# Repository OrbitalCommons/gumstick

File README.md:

# Gumstick: ESP32 + iCE40 FPGA module

A small "gumstick" daughterboard that pairs an Espressif ESP32 (Wi-Fi, USB,
application CPU) with a Lattice iCE40UP5K FPGA (timing-critical I/O), plus the
carrier used to program and test it. KiCad 10 sources, fabrication outputs,
interface control documents and the scripts that generated them.

| Folder | Design | Status |
|---|---|---|
| [`current-df40-connectors/`](current-df40-connectors/README.md) | **v1, current.** 20 × 45 mm, 4 layers, ESP32-S2FH4 + iCE40UP5K-SG48, U.FL antenna jack, RGB LED, two underside Hirose DF40 40-pin board-to-board connectors (one receptacle, one plug, so it cannot mate reversed). | First 10 ordered; the exact ordered files are frozen in [`releases/v1/`](current-df40-connectors/releases/v1/README.md) and Git tag `v1`. |
| [`future-m2-goldfingers/`](future-m2-goldfingers/README.md) | **v2, future.** 22 × 42 mm M.2 2242 key-M card (0.8 mm, 4 layers) with gold-finger contacts and a custom pinout; bare ESP32-C6 + 16 MB QSPI flash + the same iCE40UP5K. Not PCIe/NVMe compatible. | Development draft, not for fabrication. |
| [`programming-carrier/`](programming-carrier/README.md) | USB programmer and slow-GPIO indicator fixture for the v1 module (mating DF40 pair, buttons, LEDs). | v1 ordered. |

Start with the **[v1 interface control document](current-df40-connectors/docs/ICD-v1.md)**
when designing a carrier for the module: it is the electrical and mechanical
contract (pinout, mated height, keep-outs, reusable footprints).

## Renders and 3D views

Rendered with KiCad 10 (`kicad-cli pcb render`) from the board files in this
repository. Click an STL link to open GitHub's interactive 3D viewer (board,
pads and component bodies; untextured).

### v1: ESP32-S2 + iCE40, DF40 connectors (current)

3D: [current-df40-connectors.stl](https://github.com/OrbitalCommons/gumstick/blob/main/current-df40-connectors/renders/current-df40-connectors.stl)

### v2: ESP32-C6 + iCE40, M.2 gold fingers (future)

3D: [future-m2-goldfingers.stl](https://github.com/OrbitalCommons/gumstick/blob/main/future-m2-goldfingers/renders/future-m2-goldfingers.stl)

### Programming carrier

3D: [programming-carrier.stl](https://github.com/OrbitalCommons/gumstick/blob/main/programming-carrier/renders/programming-carrier.stl)

Colour 3D models with tracks, soldermask and silkscreen are next to each STL
as `renders/<folder>.glb` (open in any glTF viewer, e.g. Blender or a browser
glTF viewer); v1 also has a STEP model in `current-df40-connectors/fab/`.

## Known carriers

- [StratumZero](https://github.com/OrbitalCommons/stratumzero)
  (OrbitalCommons, currently private): a GNSS-disciplined reference clock you
  can point a camera at, built around the v1 module.

## Working on the designs (kicadmium)

These boards are set up for the
[kicadmium](https://github.com/meawoppl/agent-portal-plugins/tree/main/kicadmium)
Agent Portal plugin. [`.kicad-pcb.json`](.kicad-pcb.json) declares the three
projects (`esp32-fpga-module`, `esp32-fpga-module-v2`, `programming-carrier`)
and the quality profile in [`docs/pcb-playbook/`](docs/pcb-playbook/README.md);
[`AGENTS.md`](AGENTS.md) has the one-time setup. Then:

```sh
agent-portal plugin open kicadmium        # open the workbench, add ?project=esp32-fpga-module
kicadmium drc --json --cwd . --project esp32-fpga-module
kicadmium kct -- lint run current-df40-connectors/module.kicad_pcb --format json > /tmp/lint.json
```

Each board folder is self-contained: its symbol and footprint libraries
(`Module.pretty`, `Module.kicad_sym`, ...) and 3D models live beside the board
and are referenced through `${KIPRJMOD}`. Datasheets cited by the designs are
in [`libraries/datasheets/`](libraries/datasheets/README.md).

## Scripts

`tools/hardware/` holds the Python (KiCad `pcbnew`) and C++ helpers used to
place, route, audit and export the boards. They are kept for reproducibility
and are not required to open or fabricate the designs. A few of the earliest
v1 scripts (`extract_module.py`, `build_placement.py`, `add_rgb.py`) read the
original MainBoard import the module was extracted from; that reference board
remains in [meawoppl/bp-test](https://github.com/meawoppl/bp-test/tree/master/boards/mainboard-reference).

## History

This repository was split out of [meawoppl/bp-test](https://github.com/meawoppl/bp-test)
with history preserved for these paths. Folder moves:
`boards/esp32-fpga-module` → `current-df40-connectors`,
`boards/esp32-fpga-module-v2` → `future-m2-goldfingers`,
`boards/programming-carrier` → `programming-carrier`.

## License

[MIT](LICENSE). Third-party datasheets and vendor 3D models included for
reference keep their own terms; see `NOTICE`.

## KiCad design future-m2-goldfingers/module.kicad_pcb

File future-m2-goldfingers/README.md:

# ESP32-C6 + iCE40UP5K M.2 module (v2, development draft)

Successor to `current-df40-connectors`: the same iCE40UP5K-SG48 FPGA and QSPI configuration link,
with the ESP32-S2 module replaced by a bare ESP32-C6 (QFN40) plus a 16 MB quad SPI flash, and the board-to-board connector replaced
by an M.2 2242 key-M card edge with a custom pinout. **Not PCIe/NVMe compatible. Not for fabrication yet.**

| Item | Value |
| --- | --- |
| Card | 22 x 42 mm, 0.8 mm (M.2 0.8 +/- 0.08), 4 layers, JLCPCB JLC04081H-3313 (nominal 0.799 mm) |
| Layers | F.Cu parts and signals, In1 GND, In2 +3.3 V (with a +1.2 V island under U2), B.Cu ESP bus and FPGA lanes |
| Contacts | 67 (positions 59-66 are the key notch); pinout in `docs/icd-v2-pinout.csv` |
| Power in | +3.3 V on 2/4/70/72/74, GND on 1/3/9/15/21/27/39/45/51/57/71/73/75 (33 now carries ESP_GPIO4) |
| MCU | ESP32-C6 QFN40 (U1), external 16 MB W25Q128JV flash (U4, QIO); 13 GPIOs + USB + EN on the connector |
| Core | TLV75512 1.2 V LDO (U3), PLL fed through L2 |
| RF | ESP32-C6 pin 1 -> C1/L3/C2 pi match -> U.FL J3, 50 ohm coated CPWG 0.14 mm / 0.15 mm gap on 0.0994 mm 3313 prepreg (`docs/rf-feed.json`); match values still to re-tune |

## Files

- `module.kicad_pro/.kicad_sch/.kicad_pcb`, `module.kicad_dru`, `Module2.pretty/`, `Module2.kicad_sym`, `3dmodels/`.
- `docs/design-contract.json`: what was agreed before layout plus the final pin/contact tables.
- `docs/icd-v2-pinout.csv`: every contact with its side (odd = front copper, even = back copper), signal, IC pad and constraint.
- `docs/c6-fpga-link.csv`: the ESP32-C6 GPIO / QFN40 pad / SG48 pad mapping of the configuration link.
- `docs/contact-assignment.json`, `docs/circuit.json`, `docs/placement.json`: generator outputs.
- `docs/validation.json`, `docs/module-schematic.pdf`, `docs/module-*.svg`: checks and review exports.

## Regenerating

```sh
/usr/bin/python3 tools/hardware/build_module_v2.py --replace-draft   # libraries, placement, outline, zones, project settings
/usr/bin/python3 tools/hardware/module_v2_route.py                   # all copper, +1.2 V island, lint via roles
/usr/bin/python3 tools/hardware/module_v2_schematic.py               # symbols and schematic from docs/circuit.json
/usr/bin/python3 tools/hardware/module_v2_docs.py                    # ICD CSVs and contract tables from the board
/usr/bin/python3 tools/hardware/check_module_v2.py                   # ERC, parity DRC, PDF/SVG exports
```

## Known compromises (see `layout.deviations` in the contract)

- Eight ground vias sit in the two exposed pads. The playbook forbids vias under packages; a grounded exposed pad has no other return path, so these are kept deliberately.
- C48, C50 (FPGA VCCIO_2 / VCC east) and C39 (VDDA1) return to ground through the front pour rather than a dedicated via.
- The 3.3 V input bulk sits at the power contacts: C67/C60 feed straight into the contact 70/72 vias, C61/C66 into the contact 2 via.
- Decoupling further than 2 mm: U2 pin 5 (2.9 mm), U2 pin 29 (2.9 mm), U2 pin 33 (3.7 mm, plane via at the pin), U1 VDDA3P3 (3.6 mm to the pi filter), U1 VDDPST1 (2.7 mm) and VDDPST2 (2.4 mm), both boxed in by the 0.4 mm-pitch fan-out. Each of these pins has an I/O exit on both neighbours at 0.5 mm pitch, so only a cap lying on the pin's own line fits and adjacent lines cannot both carry one; the contract records the per-pin reason.
- The QSPI link runs through the GPIO matrix on every lane (no native FSPI pins are free of strapping/USB duties); verify the achievable configuration clock.
- The flash (U4, W25Q128JVPIQ) runs from the 3.3 V plane and the ESP's VDD_SPI pin is left unconnected: that pin sits between the flash data pins, so its 0.1/1 uF pair has no room. U4 has 0.1 uF at its supply pin and C33 (10 uF) 4 mm away.
- The flash pin order is mirrored against the ESP's SPI pins, so WP and DO cross under CS on the back layer above U4 (four vias).
- L5 (24 nH, 0201) still needs an LCSC part number.

## Card edge (JLCPCB gold-finger rules, see `layout.card_edge` in the contract)

- ENIG finish with the gold-finger option; 30 degree bevel (JLCPCB offers 30/45, the M.2 drawing shows 20: confirm socket fit).
- Fingers stop 0.6 mm inside the routed edge (JLCPCB's copper setback for a 30 degree bevel, scaled from 1.13 mm at 1.6 mm); their inner ends stay at 2.0 / 2.5 mm.
- The finger field has one solder-mask window per side and a rule area that keeps pours and vias out of it.
- JLCPCB needs at least 50 x 50 mm for a board with gold fingers (and >= 5 x 5 cm for a chamfer), so the 22 x 42 mm card must be ordered as a panel with the connector edge on the panel outline and no V-cut through the fingers.

## Stackup

- M.2 fixes the card at 0.8 +/- 0.08 mm. JLCPCB's 0.8 mm four-layer builds range from 0.721 to 0.803 mm nominal, and their tolerance below 1.0 mm is +/- 0.1 mm. JLC04081H-3313 (0.799 mm) is the best-centred build; order it by name with impedance control and confirm the finished thickness over the fingers.
- Layers: 35 um Cu / 0.0994 mm 3313 prepreg (er 4.1) / In1 GND / 0.5 mm core / In2 +3.3 V / 0.0994 mm 3313 / 35 um Cu.
- The RF width comes from `tools/hardware/module_v2_impedance.py`: JLCPCB's coated-CPWG calculator gives 50.4 ohm and a 2D field solve 49.9 ohm for 0.14 mm / 0.15 mm.

## Open before any fabrication

Carrier design and socket fit (TE 1-2199230-6), 0.8 mm stackup selection and RF/USB re-calculation, antenna match,
finger plating/bevel confirmation against the socket drawing, firmware bring-up of the C6 target.

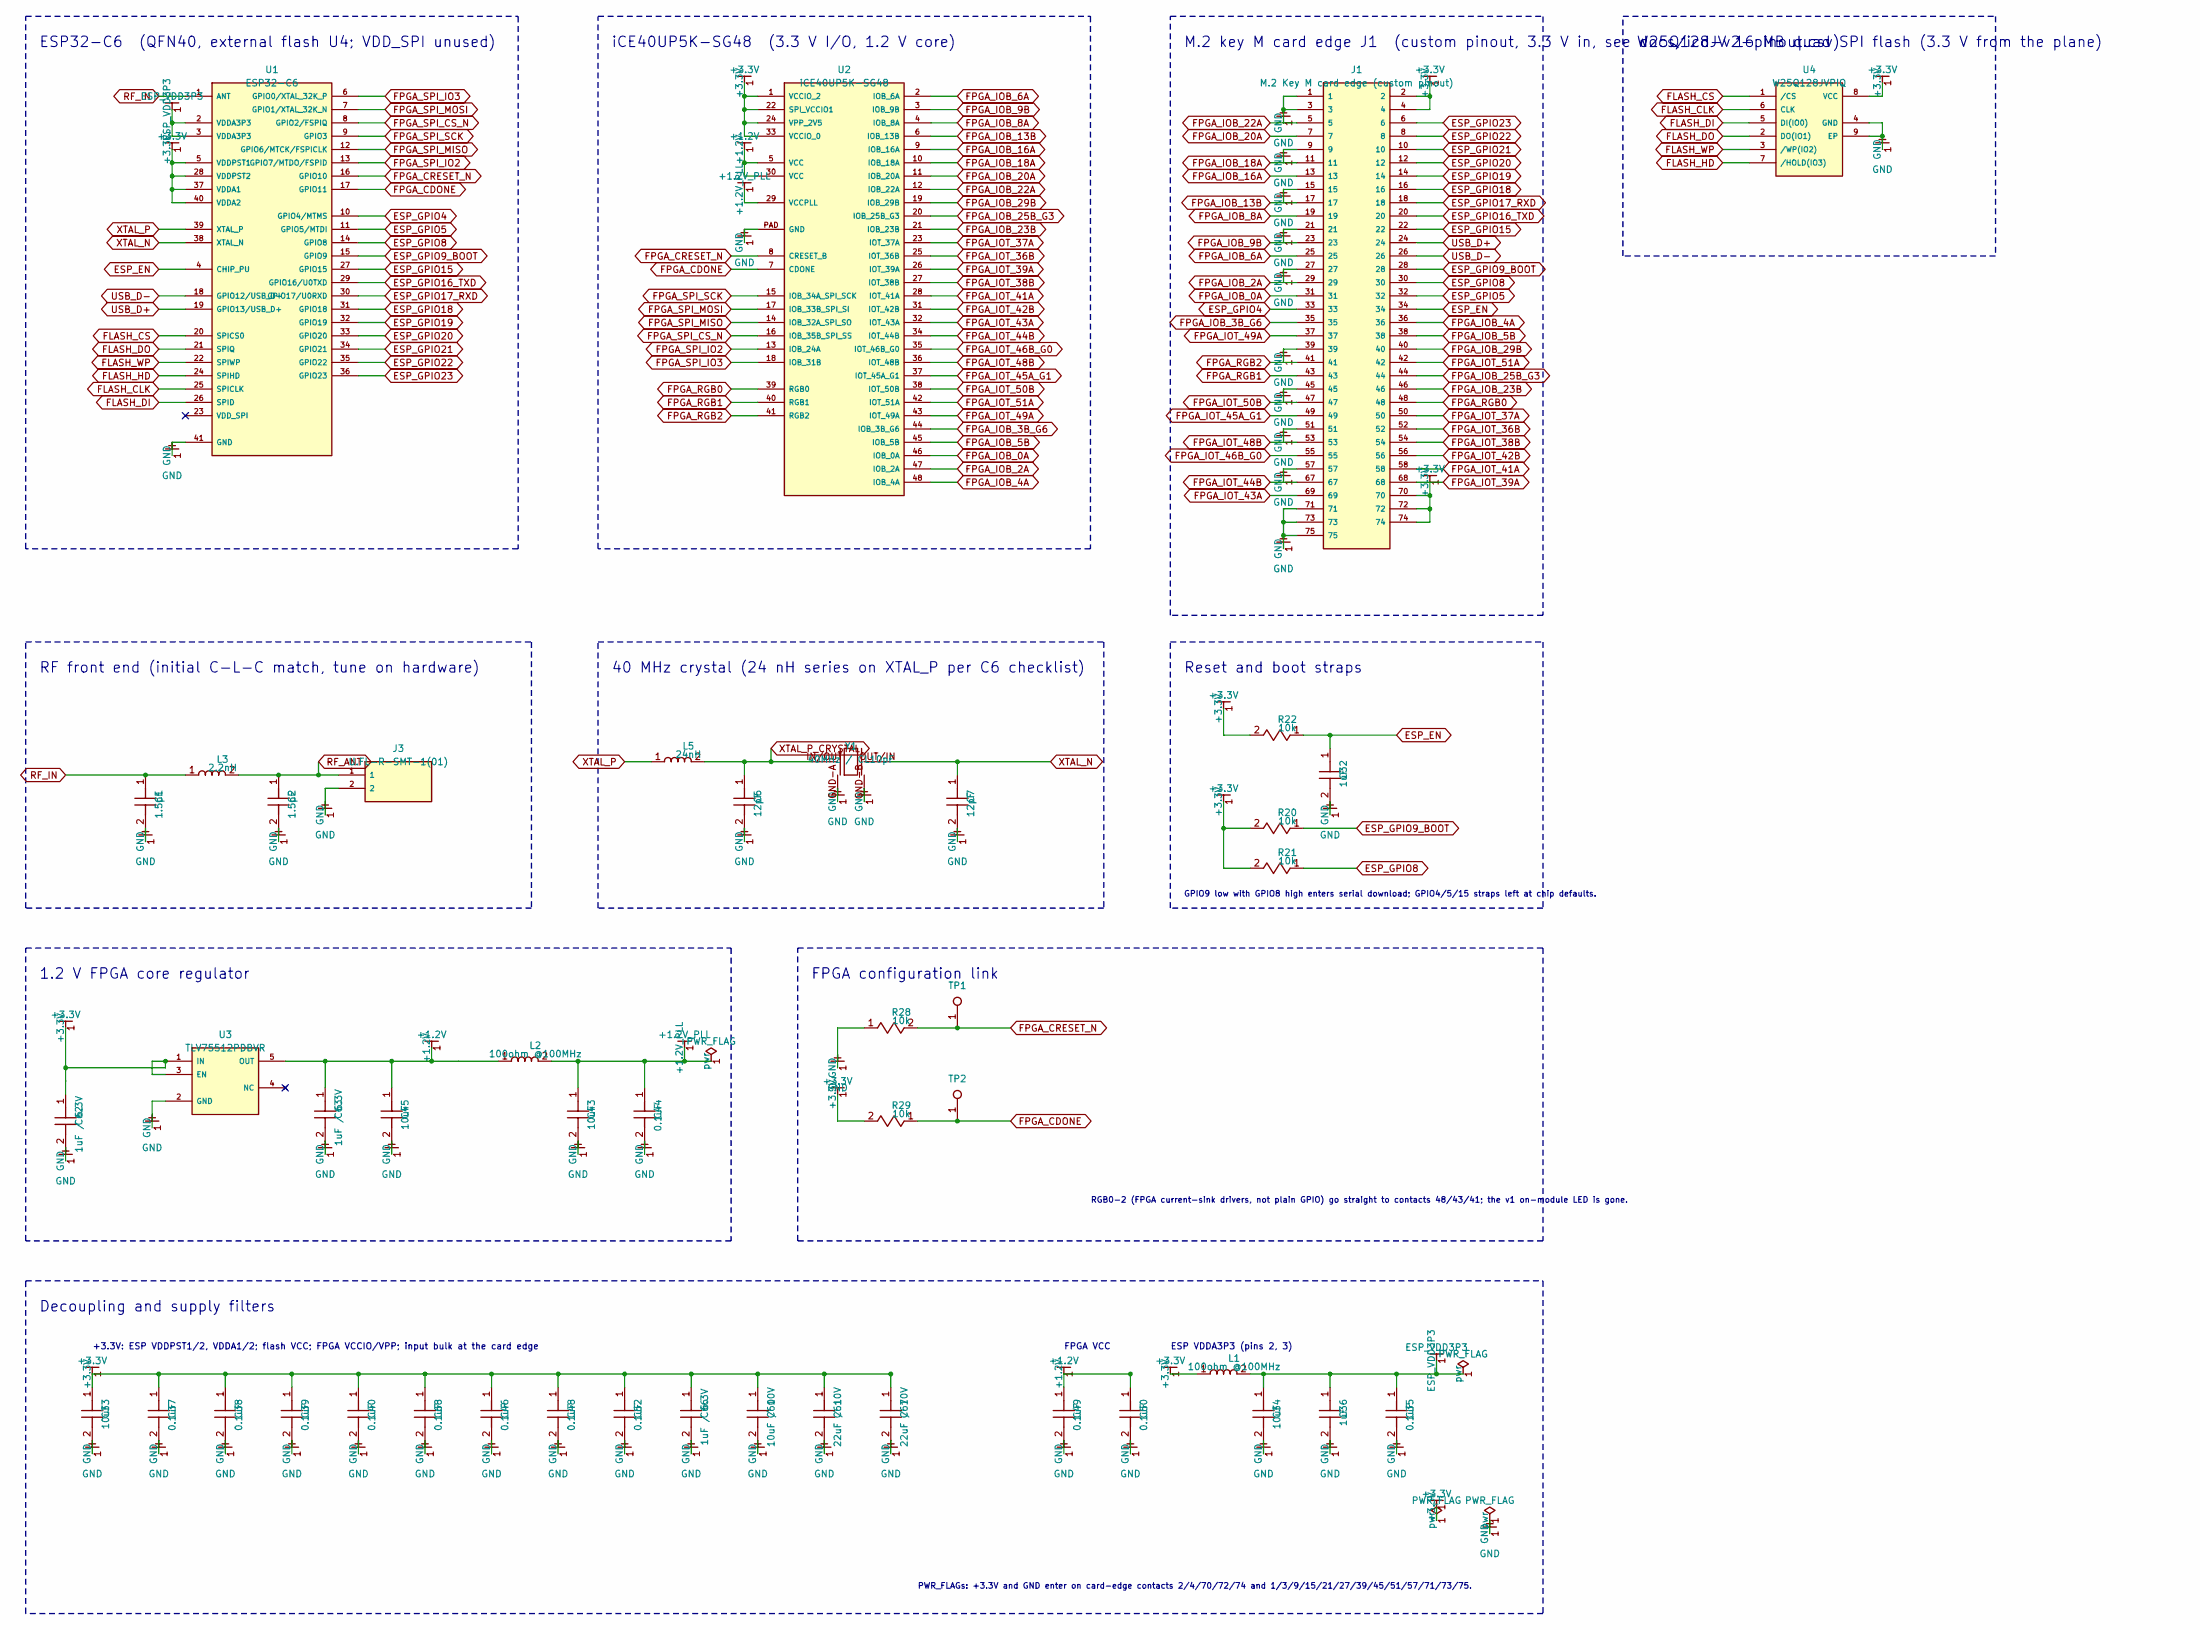
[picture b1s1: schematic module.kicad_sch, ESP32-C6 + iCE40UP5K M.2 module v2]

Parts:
C1, C2: 1.5pF; C_0402
C6, C7: 12pF; C_0402
C32, C36: 1uF; C_0402
C33, C34, C43, C45: 10uF; C_0603
C35, C37, C38, C40, C44, C46, C48, C49, C50, C52: 0.1uF; C_0402
C39, C68: 0.1uF; C_0201
C60: 10uF / 10V; C_0603
C61, C67: 22uF / 10V; C_0603
C62, C63, C66: 1uF / 6.3V; C_0603
J1: M.2 Key M card edge (custom pinout); M2_CardEdge_KeyM_2242
J3: U.FL-R-SMT-1(01); UFL_Vertical
L1, L2: 100ohm @100MHz; L_0603
L3: 2.2nH; L_0402
L5: 24nH; L_0201
R20, R21, R22, R28, R29: 10k; R_0402
TP1: FPGA_CRESET_N; TestPoint_0p8
TP2: FPGA_CDONE; TestPoint_0p8
U1: ESP32-C6; QFN-40-1EP_5x5mm_P0.4mm_EP3.3x3.3mm
U2: iCE40UP5K-SG48; ICE40-QFN
U3: TLV75512PDBVR; SOT-23-5
U4: W25Q128JVPIQ; WSON-8-1EP_6x5mm_P1.27mm_EP3.4x4.3mm
Y1: 40MHz / CL10pF; Crystal_2520_4pin

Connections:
+1.2V: C45.1, C49.1, C50.1, C63.1, L2.1, U2.5 (VCC), U2.30 (VCC), U3.5 (OUT)
+1.2V_PLL: C43.1, C44.1, L2.2, U2.29 (VCCPLL)
ESP_EN: C32.1, J1.34, R22.1, U1.4 (CHIP_PU)
ESP_GPIO4: J1.33, U1.10 (GPIO4/MTMS)
ESP_GPIO5: J1.32, U1.11 (GPIO5/MTDI)
ESP_GPIO8: J1.30, R21.1, U1.14 (GPIO8)
ESP_GPIO9_BOOT: J1.28, R20.1, U1.15 (GPIO9)
ESP_GPIO15: J1.22, U1.27 (GPIO15)
ESP_GPIO16_TXD: J1.20, U1.29 (GPIO16/U0TXD)
ESP_GPIO17_RXD: J1.18, U1.30 (GPIO17/U0RXD)
ESP_GPIO18: J1.16, U1.31 (GPIO18)
ESP_GPIO19: J1.14, U1.32 (GPIO19)
ESP_GPIO20: J1.12, U1.33 (GPIO20)
ESP_GPIO21: J1.10, U1.34 (GPIO21)
ESP_GPIO22: J1.8, U1.35 (GPIO22)
ESP_GPIO23: J1.6, U1.36 (GPIO23)
ESP_VDD3P3: C34.1, C35.1, C36.1, L1.2, U1.2 (VDDA3P3), U1.3 (VDDA3P3)
FLASH_CLK: U1.25 (SPICLK), U4.6 (CLK)
FLASH_CS: U1.20 (SPICS0), U4.1 (/CS)
FLASH_DI: U1.26 (SPID), U4.5 (DI(IO0))
FLASH_DO: U1.21 (SPIQ), U4.2 (DO(IO1))
FLASH_HD: U1.24 (SPIHD), U4.7 (/HOLD(IO3))
FLASH_WP: U1.22 (SPIWP), U4.3 (/WP(IO2))
FPGA_CDONE: R29.1, TP2.1, U1.17 (GPIO11), U2.7 (CDONE)
FPGA_CRESET_N: R28.2, TP1.1, U1.16 (GPIO10), U2.8 (CRESET_B)
FPGA_IOB_0A: J1.31, U2.46 (IOB_0A)
FPGA_IOB_3B_G6: J1.35, U2.44 (IOB_3B_G6)
FPGA_IOB_4A: J1.36, U2.48 (IOB_4A)
FPGA_IOB_5B: J1.38, U2.45 (IOB_5B)
FPGA_IOB_6A: J1.25, U2.2 (IOB_6A)
FPGA_IOB_8A: J1.19, U2.4 (IOB_8A)
FPGA_IOB_16A: J1.13, U2.9 (IOB_16A)
FPGA_IOB_20A: J1.7, U2.11 (IOB_20A)
FPGA_IOB_23B: J1.46, U2.21 (IOB_23B)
FPGA_IOB_25B_G3: J1.44, U2.20 (IOB_25B_G3)
FPGA_IOB_29B: J1.40, U2.19 (IOB_29B)
FPGA_IOT_36B: J1.52, U2.25 (IOT_36B)
FPGA_IOT_37A: J1.50, U2.23 (IOT_37A)
FPGA_IOT_38B: J1.54, U2.27 (IOT_38B)
FPGA_IOT_41A: J1.58, U2.28 (IOT_41A)
FPGA_IOT_42B: J1.56, U2.31 (IOT_42B)
FPGA_IOT_43A: J1.69, U2.32 (IOT_43A)
FPGA_IOT_45A_G1: J1.49, U2.37 (IOT_45A_G1)
FPGA_IOT_46B_G0: J1.55, U2.35 (IOT_46B_G0)
FPGA_IOT_49A: J1.37, U2.43 (IOT_49A)
FPGA_IOT_51A: J1.42, U2.42 (IOT_51A)
FPGA_RGB0: J1.48, U2.39 (RGB0)
FPGA_RGB1: J1.43, U2.40 (RGB1)
FPGA_SPI_CS_N: U1.8 (GPIO2/FSPIQ), U2.16 (IOB_35B_SPI_SS)
FPGA_SPI_IO2: U1.13 (GPIO7/MTDO/FSPID), U2.13 (IOB_24A)
FPGA_SPI_IO3: U1.6 (GPIO0/XTAL_32K_P), U2.18 (IOB_31B)
FPGA_SPI_MISO: U1.12 (GPIO6/MTCK/FSPICLK), U2.14 (IOB_32A_SPI_SO)
FPGA_SPI_MOSI: U1.7 (GPIO1/XTAL_32K_N), U2.17 (IOB_33B_SPI_SI)
FPGA_SPI_SCK: U1.9 (GPIO3), U2.15 (IOB_34A_SPI_SCK)
RF_ANT: C2.1, J3.1, L3.2
RF_IN: C1.1, L3.1, U1.1 (ANT)
USB_D+: J1.24, U1.19 (GPIO13/USB_D+)
USB_D-: J1.26, U1.18 (GPIO12/USB_D-)
XTAL_N: C7.1, U1.38 (XTAL_N), Y1.OUT/IN
XTAL_P: L5.1, U1.39 (XTAL_P)
XTAL_P_CRYSTAL: C6.1, L5.2, Y1.IN/OUT

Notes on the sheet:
ESP32-C6 (QFN40, external flash U4; VDD_SPI unused)
W25Q128JV 16 MB quad SPI flash (3.3 V from the plane)
iCE40UP5K-SG48 (3.3 V I/O, 1.2 V core)
M.2 key M card edge J1 (custom pinout, 3.3 V in, see docs/icd-v2-pinout.csv)
RF front end (initial C-L-C match, tune on hardware)
40 MHz crystal (24 nH series on XTAL_P per C6 checklist)
Reset and boot straps
GPIO9 low with GPIO8 high enters serial download; GPIO4/5/15 straps left at chip defaults.
1.2 V FPGA core regulator
FPGA configuration link
RGB0-2 (FPGA current-sink drivers, not plain GPIO) go straight to contacts 48/43/41; the v1 on-module LED is gone.
Decoupling and supply filters
+3.3V: ESP VDDPST1/2, VDDA1/2; flash VCC; FPGA VCCIO/VPP; input bulk at the card edge
FPGA VCC
ESP VDDA3P3 (pins 2, 3)
PWR_FLAGs: +3.3V and GND enter on card-edge contacts 2/4/70/72/74 and 1/3/9/15/21/27/39/45/51/57/71/73/75.

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
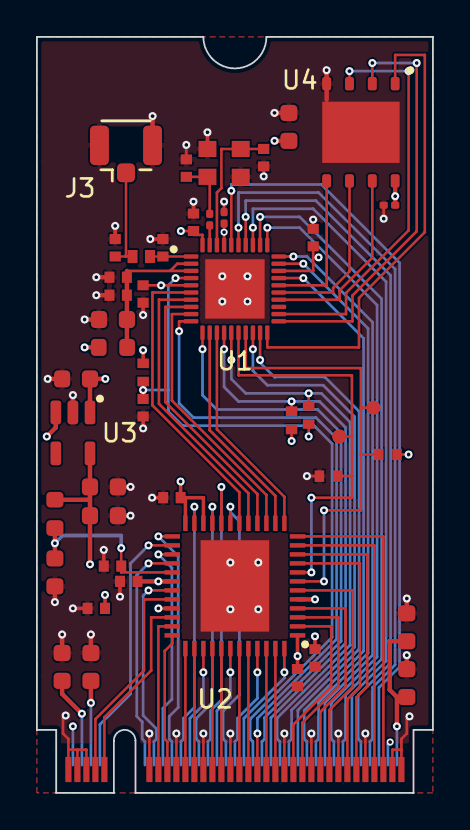
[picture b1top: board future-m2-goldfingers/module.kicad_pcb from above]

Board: 4 copper layers, 22.0 x 42.0 mm, 46 parts (0 on the bottom side), 73 nets.

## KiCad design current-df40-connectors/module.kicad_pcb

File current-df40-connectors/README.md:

# ESP32 + FPGA module

**For new carriers, use the [ordered-v1 interface control document](docs/ICD-v1.md).** It supersedes historical integration dimensions and pin notes below.

A 20 × 45 mm, four-layer development module extracted from the original
Eagle/Fusion MainBoard. It combines an ESP32-S2FH4 with an iCE40UP5K-SG48I,
a U.FL jack for an external antenna, an RGB indicator and onboard power regulation.
Routing is complete for the complementary connector pair and centered ICs.
Trace centerlines use 90/45-degree geometry with standardized power widths.
KiCad reports zero DRC violations, unconnected items, schematic-parity issues,
and ERC violations.
RF, thermal, and manufacturing review remain prototype validation requirements.
The [ordered v1 snapshot](releases/v1/README.md) preserves the manufactured revision.
Current working fabrication outputs and historical review notes are not a substitute for that snapshot.
The [width-cleanup report](docs/trace-width-audit/README.md) records the final
placement improvements and the clearance-limited neck-downs retained.

Two underside Hirose DF40 40-pin connectors carry power, programming and
GPIO signals. J1 is a receptacle and J2 a plug; both are horizontal. The
complementary genders prevent reversed full mating with the carrier pair. The [programming carrier](../programming-carrier/README.md) supplies USB, buttons
and mating connectors; the [StratumZero](https://github.com/OrbitalCommons/stratumzero/blob/main/boards/stratumzero/README.md) is a separate application carrier.

## Power

The board takes 5 V from the carrier. U3 produces 3.3 V; U4 produces the
FPGA's 1.2 V core supply. All FPGA I/O banks use 3.3 V. The optional 1.8 V
regulator and voltage-selection jumper have been removed.

L1 and L2 are Murata BLM18KG101TN1D **0603 ferrite beads, 100 ohm at 100 MHz**,
not 1 nH inductors. They form the ESP32 and FPGA PLL supply filters.
L3 is the separate 2.2 nH RF matching inductor.

## Mechanical and assembly notes

- J1, H1 and J2 lie on the longitudinal centerline, with 25 mm connector
  spacing and the hole 12.5 mm from each connector. Use the H1-relative
  body datums in the [v1 ICD](docs/ICD-v1.md); older top-edge offsets were stale.
- U1 and U2 are centered across the 20 mm board width.
- H1 has a 3.2 mm hole and a 7 mm screw-head/spacer keepout. Match the carrier
  spacer height to the connector stack height so tightening cannot crush them.
- The ordered board uses external U.FL only. Reserve cable/plug access and
  validate the chosen antenna in the carrier/enclosure; chip-antenna notes are historical.
- Vias must remain outside component solder pads and the complete QFN package bodies.
  The via-access audit passes with no pad or QFN-body overlaps.
  Confirm the stackup and validate IC temperatures with the revised ground fanouts.
- Silkscreen keeps main IC, connector and solder-jumper references. Other
  component references remain available on fabrication layers.

D1 is the original FC-B1010RGBT-HG common-anode LED. Its RGB cathodes connect
to the FPGA's RGB current drivers and share J2 pins 26, 27 and 29. Firmware must use
those drivers correctly; the carrier pins are not unloaded independent GPIOs.

## Files

- `module.kicad_pro`, `module.kicad_sch`, `module.kicad_pcb`: active design.
- `Module.kicad_sym`, `Module.pretty`, library tables: project-local libraries.
- [3D model provenance](3dmodels/README.md): local component models; LED, antenna and power-inductor envelopes include approximations.
- [3D assembly](fab/module.glb).
- [Carrier pinout](docs/carrier-pinout.csv) and [layout notes](docs/layout-notes.md).
- [Component sourcing](docs/component-sourcing.md): selected manufacturer parts,
  supplier links and procurement caveats; the current BOM has 49 purchased placements.
- [BOM](fab/bom/module-bom.csv); [non-purchased PCB features](fab/bom/pcb-features.csv).
- `fab/checks`: ERC, DRC, via/pad overlap audit, and the schematic netlist.
- [Gerber ZIP](fab/module-gerbers.zip), [assembly BOM](fab/jlcpcb/BOM_module.csv),
  [placement CSV](fab/jlcpcb/CPL_module.csv), and [schematic PDF](fab/module-schematic.pdf).

The ESP32-C3 is not pin-compatible with the S2. It remains an architecture
option requiring a new footprint and pinout; the current design retains S2.

Original exports are preserved in `../../source/fusion`, with the native
import reference in `../mainboard-reference`. The module restores Eagle's
C49/C50 power assignments that were split by the initial native import.

TP1 exposes FPGA_CRESET_N (active-low reset); TP2 exposes FPGA_CDONE.
The application-specific SYNC_IO connection is removed. ESP GPIO38 is exposed
on J1.39 and FPGA physical pin 44 / G6 on J2.32; they are not joined on the module.
ESP32 package pins 31–36 remain unconnected externally
because they serve the S2FH4 internal flash.

See [carrier mating requirements](docs/carrier-keying.md) for the connector
MPNs, 2 mm stack, mounting-tab requirements, and carrier contact mapping.

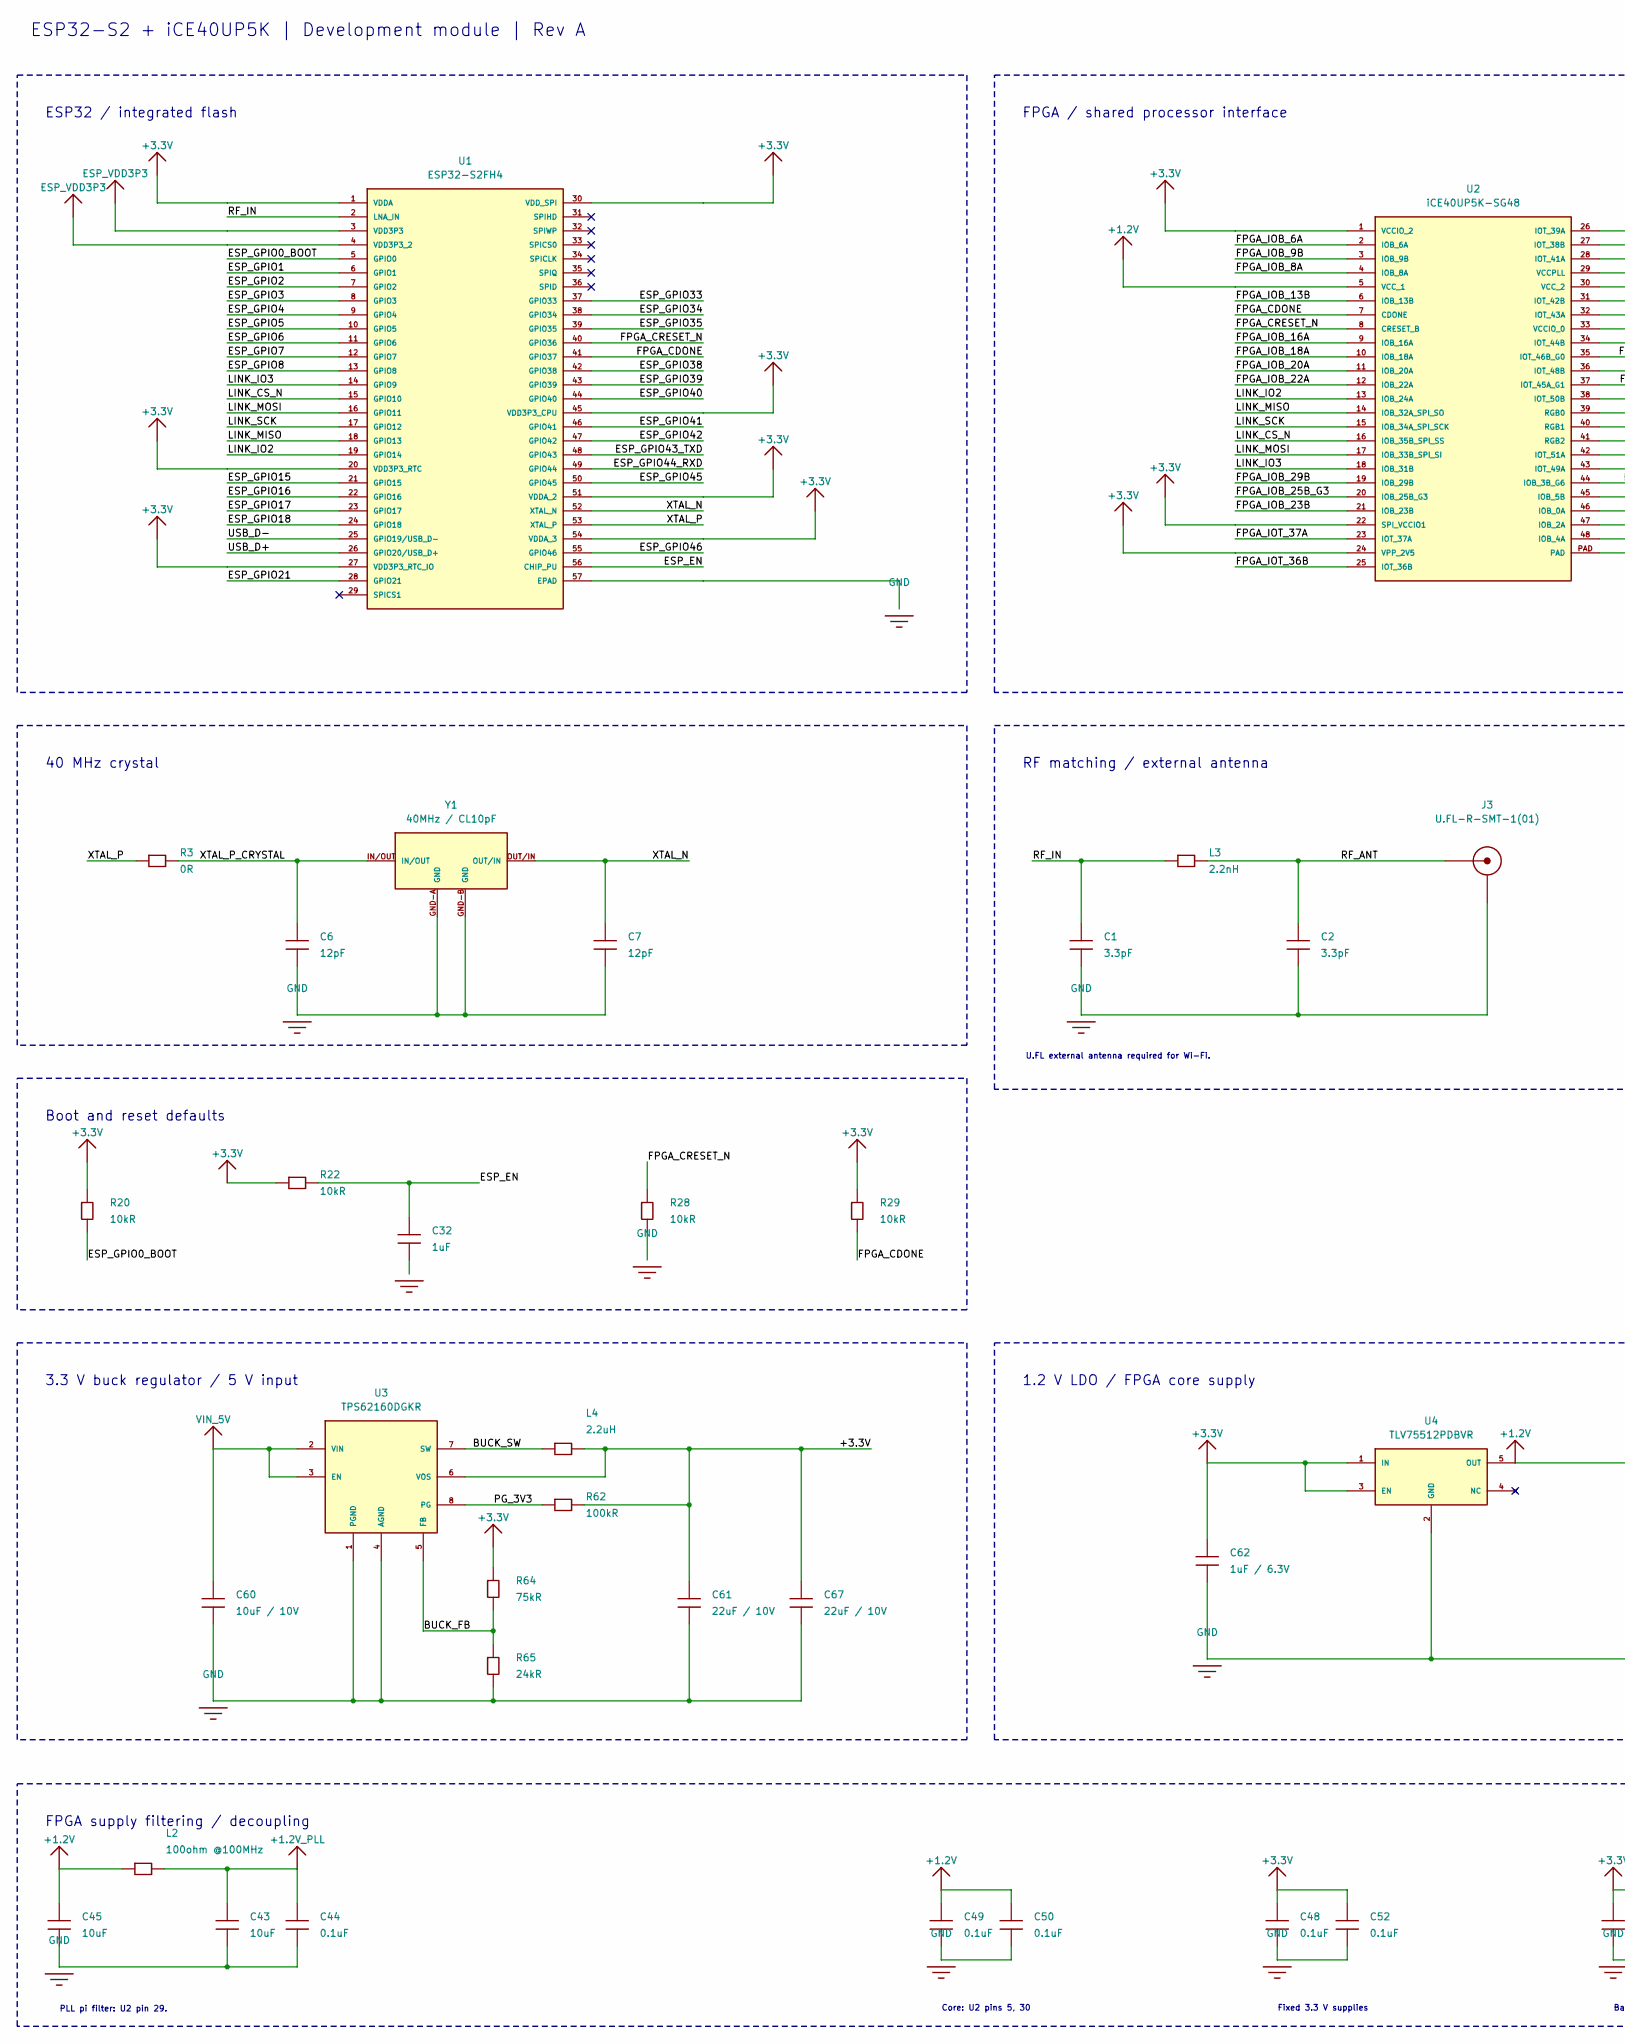
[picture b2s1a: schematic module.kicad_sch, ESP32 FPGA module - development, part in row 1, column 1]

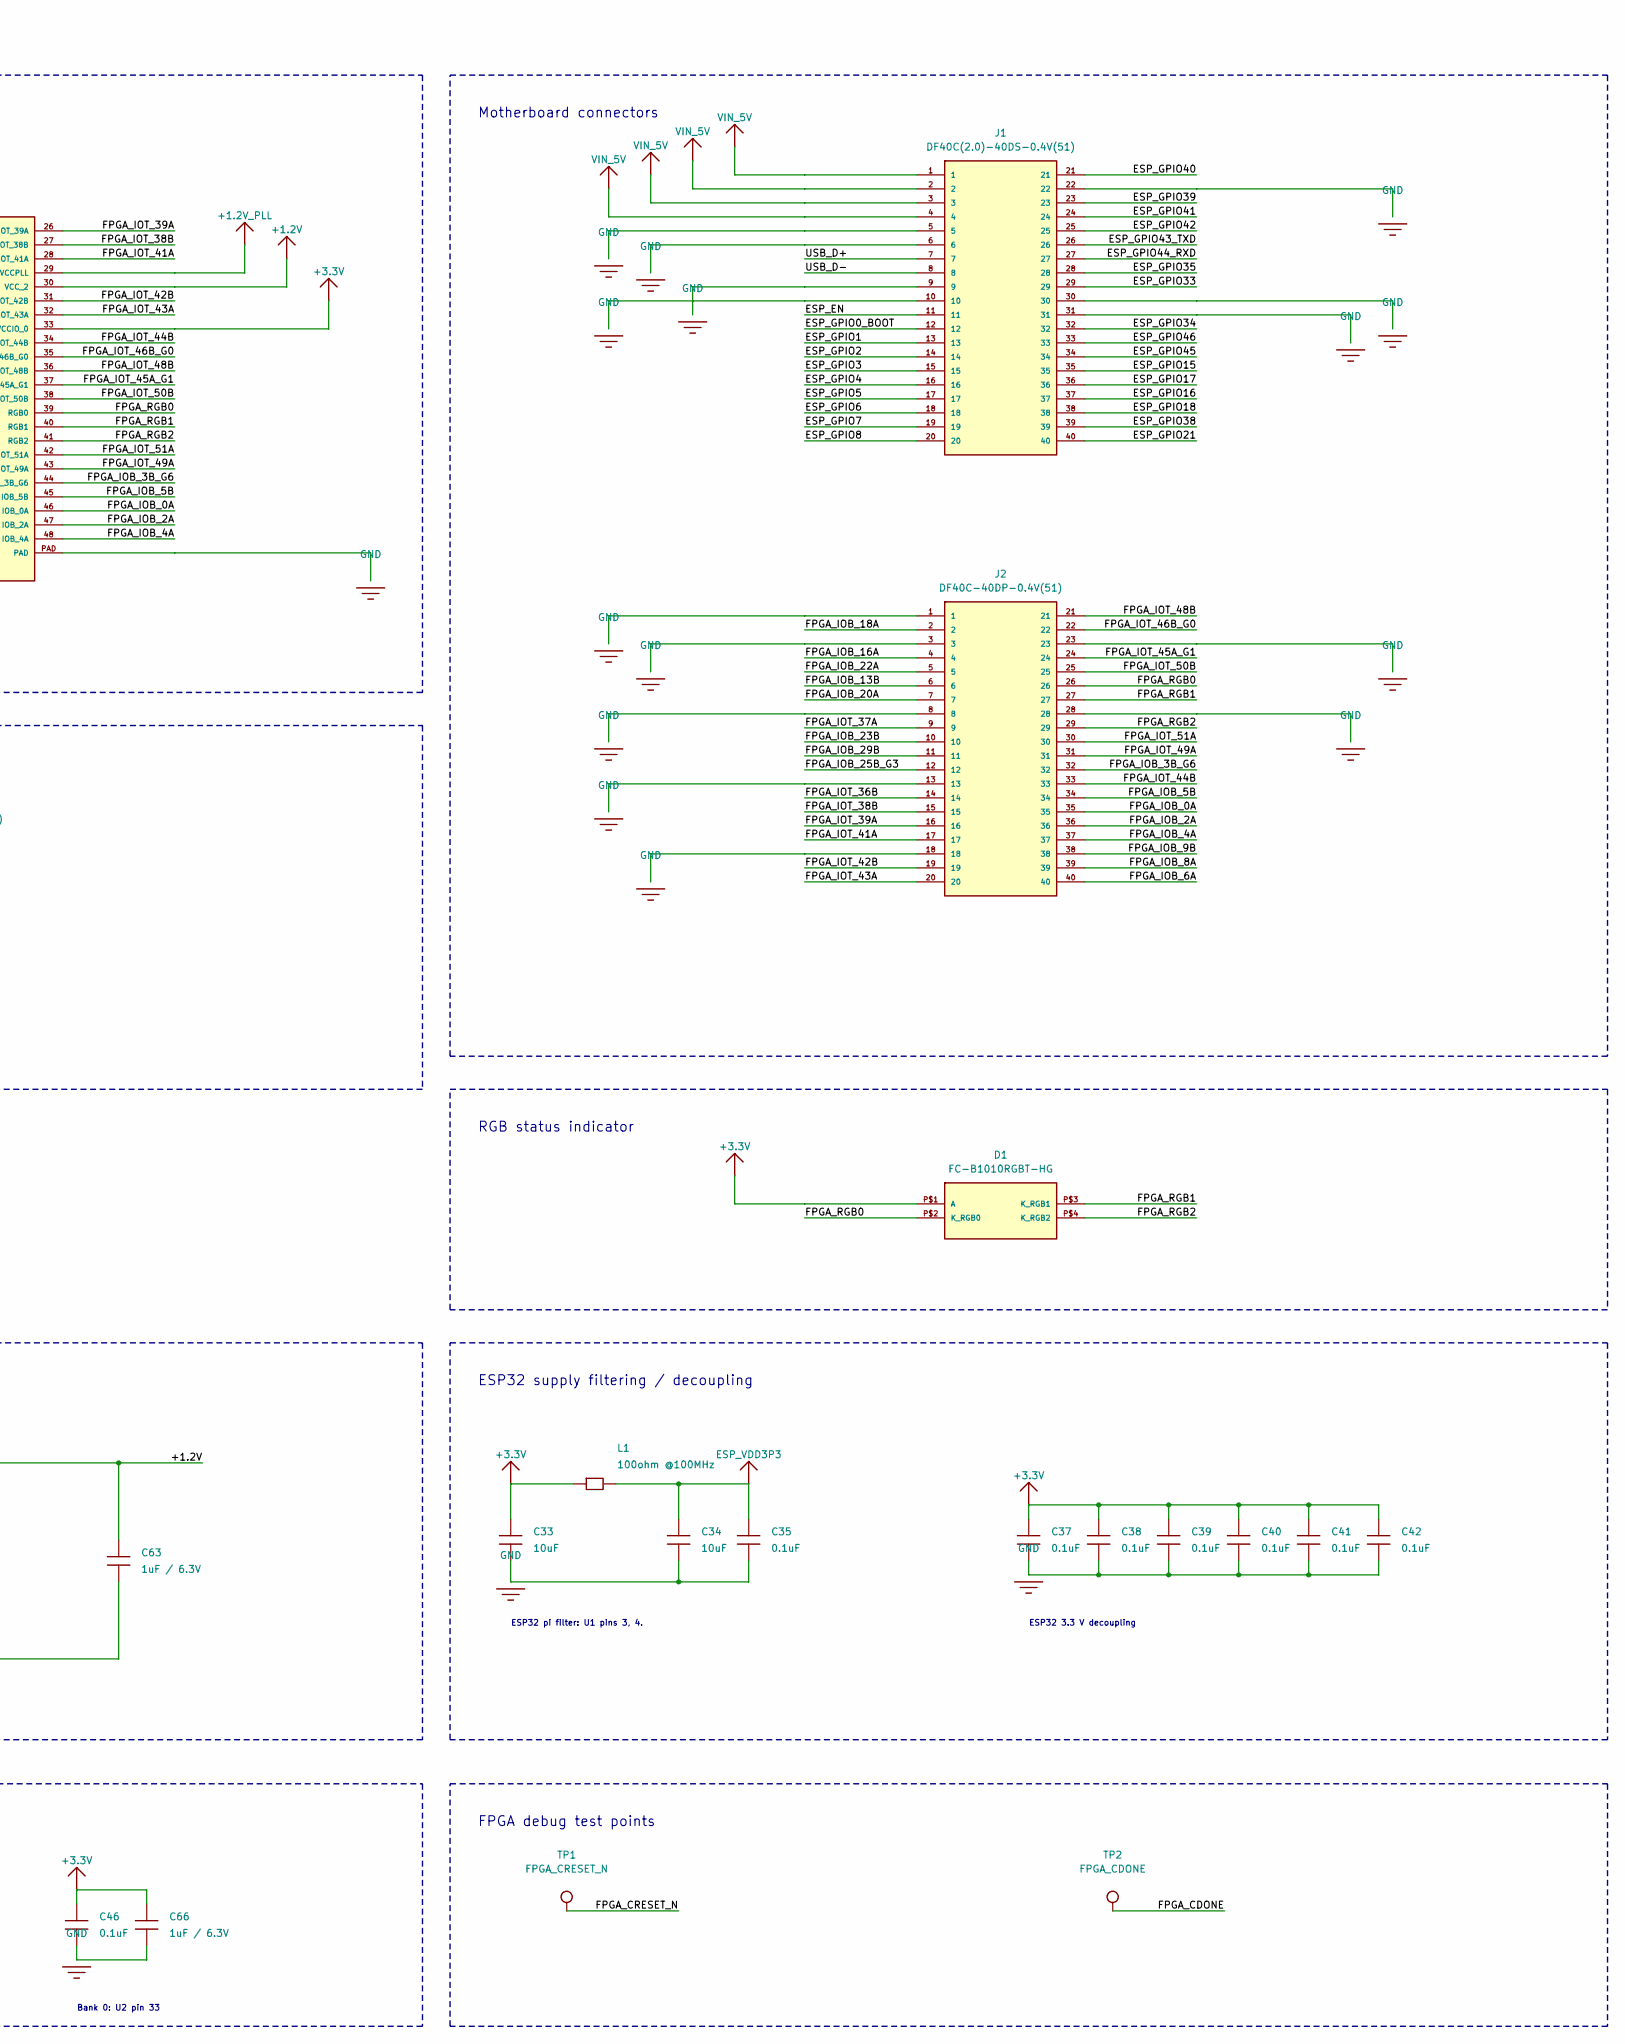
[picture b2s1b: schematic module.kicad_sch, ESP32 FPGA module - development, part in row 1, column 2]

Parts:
C1: 3.3pF; C1_CAPC1005X60; MPN GJM1555C1H3R3BB01D; LCSC C76906
C2: 3.3pF; C2_CAPC1005X60; MPN GJM1555C1H3R3BB01D; LCSC C76906
C6: 12pF; C6_CAPC1005X60; MPN CL05C120JB5NNNC; LCSC C26406
C7: 12pF; C7_CAPC1005X60; MPN CL05C120JB5NNNC; LCSC C26406
C32: 1uF; C32_CAPC1005X60; MPN CL05A105KO5NNNC; LCSC C29266
C33: 10uF; C33_C_0603_1608Metric; MPN CL10A106KP8NNNC; LCSC C19702
C34: 10uF; C34_C_0603_1608Metric; MPN CL10A106KP8NNNC; LCSC C19702
C35: 0.1uF; C35_CAPC1005X60; MPN CL05B104KO5NNNC; LCSC C1525
C37: 0.1uF; C37_CAPC1005X60; MPN CL05B104KO5NNNC; LCSC C1525
C38: 0.1uF; C38_CAPC1005X60; MPN CL05B104KO5NNNC; LCSC C1525
C39: 0.1uF; C39_CAPC1005X60; MPN CL05B104KO5NNNC; LCSC C1525
C40: 0.1uF; C40_CAPC1005X60; MPN CL05B104KO5NNNC; LCSC C1525
C41: 0.1uF; C41_CAPC1005X60; MPN CL05B104KO5NNNC; LCSC C1525
C42: 0.1uF; C42_CAPC1005X60; MPN CL05B104KO5NNNC; LCSC C1525
C43: 10uF; C43_C_0603_1608Metric; MPN CL10A106KP8NNNC; LCSC C19702
C44: 0.1uF; C44_CAPC1005X60; MPN CL05B104KO5NNNC; LCSC C1525
C45: 10uF; C45_C_0603_1608Metric; MPN CL10A106KP8NNNC; LCSC C19702
C46: 0.1uF; C46_CAPC1005X60; MPN CL05B104KO5NNNC; LCSC C1525
C48: 0.1uF; C48_CAPC1005X60; MPN CL05B104KO5NNNC; LCSC C1525
C49: 0.1uF; C49_CAPC1005X60; MPN CL05B104KO5NNNC; LCSC C1525
C50: 0.1uF; C50_CAPC1005X60; MPN CL05B104KO5NNNC; LCSC C1525
C52: 0.1uF; C52_CAPC1005X60; MPN CL05B104KO5NNNC; LCSC C1525
C60: 10uF / 10V; C60_C_0603_1608Metric; MPN CL10A106KP8NNNC; LCSC C19702
C61: 22uF / 10V; C61_C_0603_1608Metric; MPN CL10A226MPCNUBE; LCSC C5355402
C62: 1uF / 6.3V; C62_C_0603_1608Metric; MPN CL10A105KB8NNNC; LCSC C15849
C63: 1uF / 6.3V; C63_C_0603_1608Metric; MPN CL10A105KB8NNNC; LCSC C15849
C66: 1uF / 6.3V; C66_C_0603_1608Metric; MPN CL10A105KB8NNNC; LCSC C15849
C67: 22uF / 10V; C67_C_0603_1608Metric; MPN CL10A226MPCNUBE; LCSC C5355402
D1: FC-B1010RGBT-HG; D1_RGBLED; MPN FC-B1010RGBT-HG; LCSC C158099
J1: DF40C(2.0)-40DS-0.4V(51); J1_DF40C_40DS_2mm; MPN DF40C(2.0)-40DS-0.4V(51); LCSC C597934
J2: DF40C-40DP-0.4V(51); J2_DF40C_40DP; MPN DF40C-40DP-0.4V(51); LCSC C424643
J3: U.FL-R-SMT-1(01); J3_U.FL_Hirose_U.FL-R-SMT-1_Vertical; MPN U.FL-R-SMT-1(01)
L1: 100ohm @100MHz; L1_L_0603_1608Metric; MPN BLM18KG101TN1D; LCSC C160981
L2: 100ohm @100MHz; L2_L_0603_1608Metric; MPN BLM18KG101TN1D; LCSC C160981
L3: 2.2nH; L3_INDC1006X60N; MPN LQG15HS2N2S02D; LCSC C86061
L4: 2.2uH; L4_L_XFL3012_222MEC; MPN XFL3012-222MEC; LCSC C3911432
R3: 0R; R3_RESC1005X40; MPN 0402WGF0000TCE; LCSC C17168
R20: 10kR; R20_RESC1005X40; MPN RC0402FR-0710KL; LCSC C60490
R22: 10kR; R22_RESC1005X40; MPN RC0402FR-0710KL; LCSC C60490
R28: 10kR; R28_RESC1005X40; MPN RC0402FR-0710KL; LCSC C60490
R29: 10kR; R29_RESC1005X40; MPN RC0402FR-0710KL; LCSC C60490
R62: 100kR; R62_R_0402_1005Metric; MPN RC0402FR-07100KL; LCSC C60491
R64: 75kR; R64_R_0402_1005Metric; MPN 0402WGF7502TCE; LCSC C25798
R65: 24kR; R65_R_0402_1005Metric; MPN 0402WGF2402TCE; LCSC C25769
TP1: FPGA_CRESET_N; TestPoint_0p8
TP2: FPGA_CDONE; TestPoint_0p8
U1: ESP32-S2FH4; U1_QFN56_ESP32-S2FH4_EXP-M; MPN ESP32-S2FH4; LCSC C2840995
U2: iCE40UP5K-SG48; U2_ICE40-QFN; MPN ICE40UP5K-SG48I; LCSC C2678152
U3: TPS62160DGKR; U3_VSSOP-8_3x3mm_P0.65mm; MPN TPS62160DGKR; LCSC C60726
U4: TLV75512PDBVR; U4_SOT-23-5; MPN TLV75512PDBVR; LCSC C2877864
Y1: 40MHz / CL10pF; Y1_JGHC_S2240000101050; MPN S2240000101050; LCSC C426970

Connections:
+1.2V: C45.1, C49.1, C50.1, C63.1, L2.1, U2.5 (VCC_1), U2.30 (VCC_2), U4.5 (OUT)
+1.2V_PLL: C43.1, C44.1, L2.2, U2.29 (VCCPLL)
+3.3V: C33.1, C37.1, C38.1, C39.1, C40.1, C41.1, C42.1, C46.1, C48.1, C52.1, C61.1, C62.1, C66.1, C67.1, D1.P$1 (A), L1.1, L4.2, R20.2, R22.2, R29.2, R62.2, R64.1, U1.1 (VDDA), U1.20 (VDD3P3_RTC), U1.27 (VDD3P3_RTC_IO), U1.30 (VDD_SPI), U1.45 (VDD3P3_CPU), U1.51 (VDDA_2), U1.54 (VDDA_3), U2.1 (VCCIO_2), U2.22 (SPI_VCCIO1), U2.24 (VPP_2V5), U2.33 (VCCIO_0), U3.6 (VOS), U4.1 (IN), U4.3 (EN)
/BUCK_FB: R64.2, R65.1, U3.5 (FB)
/BUCK_SW: L4.1, U3.7 (SW)
/ESP_EN: C32.1, J1.11, R22.1, U1.56 (CHIP_PU)
/ESP_GPIO0_BOOT: J1.12, R20.1, U1.5 (GPIO0)
/ESP_GPIO1: J1.13, U1.6 (GPIO1)
/ESP_GPIO2: J1.14, U1.7 (GPIO2)
/ESP_GPIO3: J1.15, U1.8 (GPIO3)
/ESP_GPIO4: J1.16, U1.9 (GPIO4)
/ESP_GPIO5: J1.17, U1.10 (GPIO5)
/ESP_GPIO6: J1.18, U1.11 (GPIO6)
/ESP_GPIO7: J1.19, U1.12 (GPIO7)
/ESP_GPIO8: J1.20, U1.13 (GPIO8)
/ESP_GPIO15: J1.35, U1.21 (GPIO15)
/ESP_GPIO16: J1.37, U1.22 (GPIO16)
/ESP_GPIO17: J1.36, U1.23 (GPIO17)
/ESP_GPIO18: J1.38, U1.24 (GPIO18)
/ESP_GPIO21: J1.40, U1.28 (GPIO21)
/ESP_GPIO33: J1.29, U1.37 (GPIO33)
/ESP_GPIO34: J1.32, U1.38 (GPIO34)
/ESP_GPIO35: J1.28, U1.39 (GPIO35)
/ESP_GPIO38: J1.39, U1.42 (GPIO38)
/ESP_GPIO39: J1.23, U1.43 (GPIO39)
/ESP_GPIO40: J1.21, U1.44 (GPIO40)
/ESP_GPIO41: J1.24, U1.46 (GPIO41)
/ESP_GPIO42: J1.25, U1.47 (GPIO42)
/ESP_GPIO43_TXD: J1.26, U1.48 (GPIO43)
/ESP_GPIO44_RXD: J1.27, U1.49 (GPIO44)
/ESP_GPIO45: J1.34, U1.50 (GPIO45)
/ESP_GPIO46: J1.33, U1.55 (GPIO46)
/FPGA_CDONE: R29.1, TP2.1, U1.41 (GPIO37), U2.7 (CDONE)
/FPGA_CRESET_N: R28.2, TP1.1, U1.40 (GPIO36), U2.8 (CRESET_B)
/FPGA_IOB_0A: J2.35, U2.46 (IOB_0A)
/FPGA_IOB_2A: J2.36, U2.47 (IOB_2A)
/FPGA_IOB_3B_G6: J2.32, U2.44 (IOB_3B_G6)
/FPGA_IOB_4A: J2.37, U2.48 (IOB_4A)
/FPGA_IOB_5B: J2.34, U2.45 (IOB_5B)
/FPGA_IOB_6A: J2.40, U2.2 (IOB_6A)
/FPGA_IOB_8A: J2.39, U2.4 (IOB_8A)
/FPGA_IOB_9B: J2.38, U2.3 (IOB_9B)
/FPGA_IOB_13B: J2.6, U2.6 (IOB_13B)
/FPGA_IOB_16A: J2.4, U2.9 (IOB_16A)
/FPGA_IOB_18A: J2.2, U2.10 (IOB_18A)
/FPGA_IOB_20A: J2.7, U2.11 (IOB_20A)
/FPGA_IOB_22A: J2.5, U2.12 (IOB_22A)
/FPGA_IOB_23B: J2.10, U2.21 (IOB_23B)
/FPGA_IOB_25B_G3: J2.12, U2.20 (IOB_25B_G3)
/FPGA_IOB_29B: J2.11, U2.19 (IOB_29B)
/FPGA_IOT_36B: J2.14, U2.25 (IOT_36B)
/FPGA_IOT_37A: J2.9, U2.23 (IOT_37A)
/FPGA_IOT_38B: J2.15, U2.27 (IOT_38B)
/FPGA_IOT_39A: J2.16, U2.26 (IOT_39A)
/FPGA_IOT_41A: J2.17, U2.28 (IOT_41A)
/FPGA_IOT_42B: J2.19, U2.31 (IOT_42B)
/FPGA_IOT_43A: J2.20, U2.32 (IOT_43A)
/FPGA_IOT_44B: J2.33, U2.34 (IOT_44B)
/FPGA_IOT_45A_G1: J2.24, U2.37 (IOT_45A_G1)
/FPGA_IOT_46B_G0: J2.22, U2.35 (IOT_46B_G0)
/FPGA_IOT_48B: J2.21, U2.36 (IOT_48B)
/FPGA_IOT_49A: J2.31, U2.43 (IOT_49A)
/FPGA_IOT_50B: J2.25, U2.38 (IOT_50B)
/FPGA_IOT_51A: J2.30, U2.42 (IOT_51A)
/FPGA_RGB0: D1.P$2 (K_RGB0), J2.26, U2.39 (RGB0)
/FPGA_RGB1: D1.P$3 (K_RGB1), J2.27, U2.40 (RGB1)
/FPGA_RGB2: D1.P$4 (K_RGB2), J2.29, U2.41 (RGB2)
/LINK_CS_N: U1.15 (GPIO10), U2.16 (IOB_35B_SPI_SS)
/LINK_IO2: U1.19 (GPIO14), U2.13 (IOB_24A)
/LINK_IO3: U1.14 (GPIO9), U2.18 (IOB_31B)
/LINK_MISO: U1.18 (GPIO13), U2.14 (IOB_32A_SPI_SO)
/LINK_MOSI: U1.16 (GPIO11), U2.17 (IOB_33B_SPI_SI)
/LINK_SCK: U1.17 (GPIO12), U2.15 (IOB_34A_SPI_SCK)
/PG_3V3: R62.1, U3.8 (PG)
/RF_ANT: C2.1, J3.1 (RF), L3.2
/RF_IN: C1.1, L3.1, U1.2 (LNA_IN)
/USB_D+: J1.7, U1.26 (GPIO20/USB_D+)
/USB_D-: J1.8, U1.25 (GPIO19/USB_D-)
/XTAL_N: C7.1, U1.52 (XTAL_N), Y1.OUT/IN
/XTAL_P: R3.1, U1.53 (XTAL_P)
/XTAL_P_CRYSTAL: C6.1, R3.2, Y1.IN/OUT
ESP_VDD3P3: C34.1, C35.1, L1.2, U1.3 (VDD3P3), U1.4 (VDD3P3_2)
GND: C1.2, C2.2, C6.2, C7.2, C32.2, C33.2, C34.2, C35.2, C37.2, C38.2, C39.2, C40.2, C41.2, C42.2, C43.2, C44.2, C45.2, C46.2, C48.2, C49.2, C50.2, C52.2, C60.2, C61.2, C62.2, C63.2, C66.2, C67.2, J1.5, J1.6, J1.9, J1.10, J1.22, J1.30, J1.31, J2.1, J2.3, J2.8, J2.13, J2.18, J2.23, J2.28, J3.2 (GND), R28.1, R65.2, U1.57 (EPAD), U2.PAD, U3.1 (PGND), U3.4 (AGND), U4.2 (GND), Y1.GND-A (GND), Y1.GND-B (GND)
VIN_5V: C60.1, J1.1, J1.2, J1.3, J1.4, U3.2 (VIN), U3.3 (EN)

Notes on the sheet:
ESP32-S2 + iCE40UP5K | Development module | Rev A
ESP32 / integrated flash
FPGA / shared processor interface
Motherboard connectors
40 MHz crystal
RF matching / external antenna
U.FL external antenna required for Wi-Fi.
Boot and reset defaults
RGB status indicator
3.3 V buck regulator / 5 V input
1.2 V LDO / FPGA core supply
ESP32 supply filtering / decoupling
FPGA supply filtering / decoupling
FPGA debug test points
ESP32 pi filter: U1 pins 3, 4.
PLL pi filter: U2 pin 29.
ESP32 3.3 V decoupling
Core: U2 pins 5, 30
Fixed 3.3 V supplies
Bank 0: U2 pin 33
